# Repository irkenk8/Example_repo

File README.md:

# Example_repo
Here are all the project folders

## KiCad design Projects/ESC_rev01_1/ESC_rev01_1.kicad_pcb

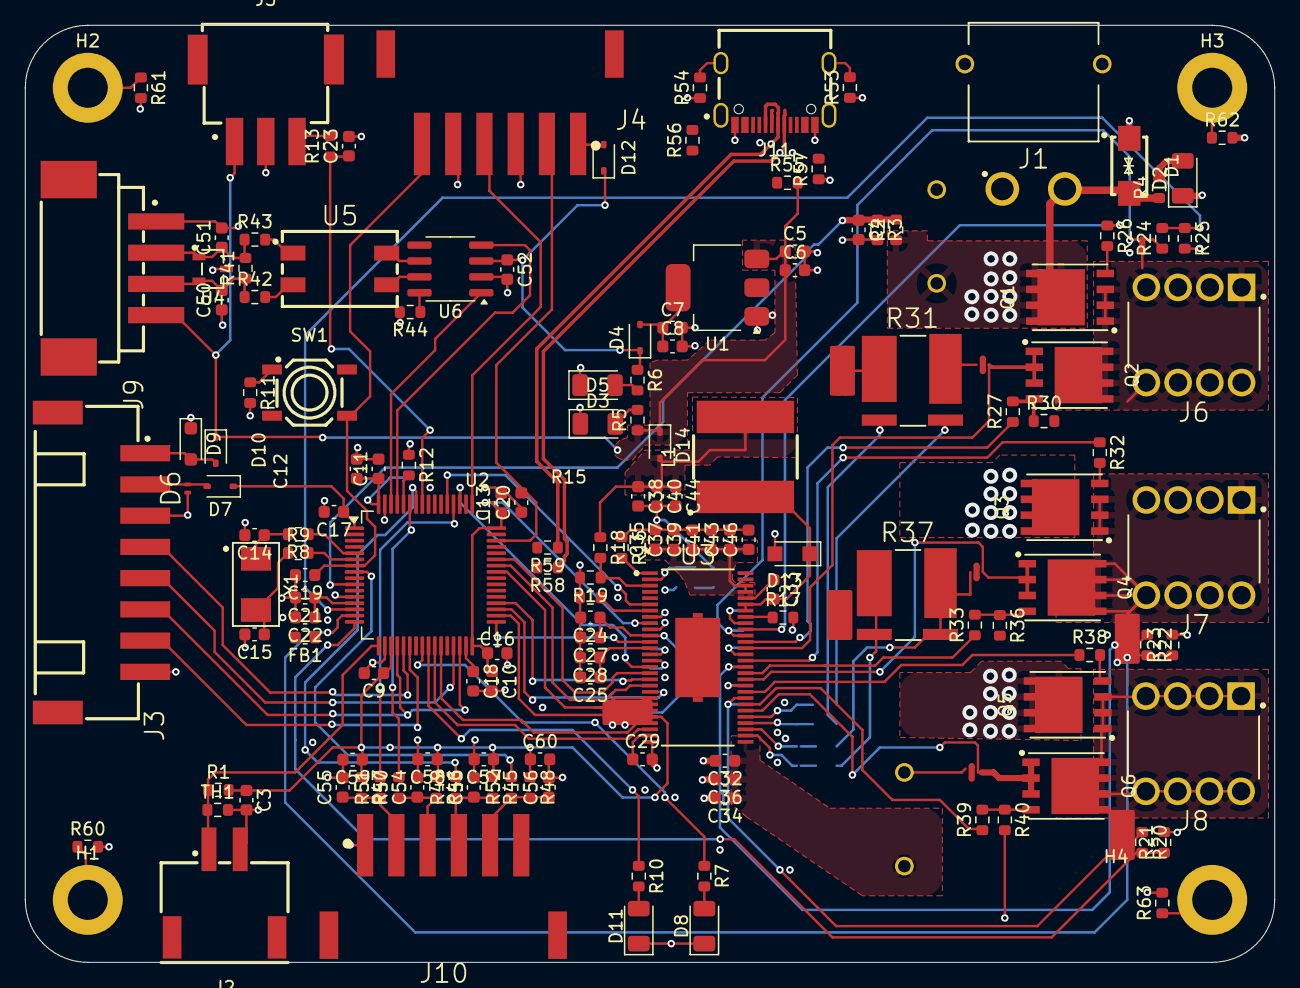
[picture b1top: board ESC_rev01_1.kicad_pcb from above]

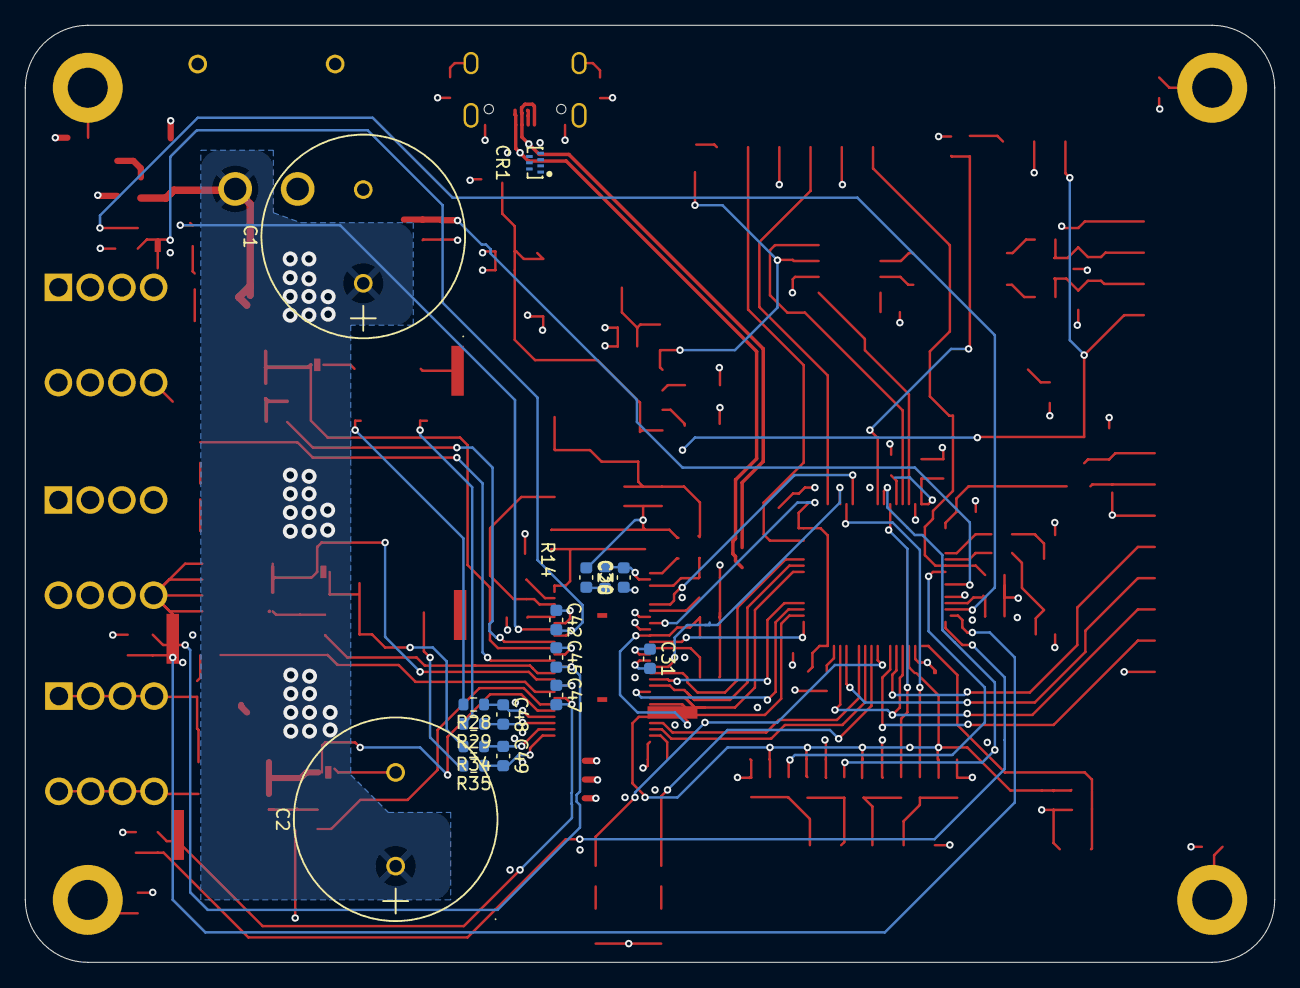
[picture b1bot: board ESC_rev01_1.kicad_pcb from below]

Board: 4 copper layers, 100.0 x 75.0 mm, 179 parts (16 on the bottom side), 125 nets.

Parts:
C1, C2: LKMI2501K821MF; CAPPRD750W80D1600H2500
C3, C4, C10, C11, C12, C13, C16, C17, C19, C21, C23, C33, C42, C45, C47, C57, C58, C59, C60: 100n; C_0603_1608Metric
C5, C6, C7, C8, C22: 1u; C_0603_1608Metric
C9, C32, C34, C35, C36, C37, C38, C39, C40, C41, C43, C44, C46: 10u; C_0603_1608Metric
C14, C15: 10p; C_0603_1608Metric
C18, C20, C24, C25, C27, C28, C29, C48, C52: 2u2; C_0603_1608Metric
C26: 6n8; C_0603_1608Metric
C30: 120p; C_0603_1608Metric
C31: 22n; C_0603_1608Metric
C49: 2n2; C_0603_1608Metric
C50, C51: 60p; C_0603_1608Metric
C53, C54, C55, C56: 4n7; C_0603_1608Metric
CR1: PUSB3AB6Z; XSON-7_L2.2-W1.2-P0.50-BL
D1: SMA6J60CA-Q; SMA_L4.4-W2.8-LS5.1-BI
D2, D3, D5, D8: LED_G; LED_1206_3216Metric
D4, D7, D10, D12, D14: BAT60A; D_SOD-323
D6: PESD3V3X1BL; D_SOD-882_BI
D9: SD05C-7; D_SOD-323_HandSoldering
D11: LED_R; LED_1206_3216Metric
D13: PMEG6020ER; Nexperia_CFP3_SOD-123W
FB1: FerriteBead; L_0603_1608Metric
H1, H2, H3, H4: MountingHole_Pad; MountingHole_3.2mm_M3_DIN965_Pad
J1: XT30PW-M; CONN-TH_XT30PW-M
J2: XH-2PWBPZ; CONN-SMD_XH-2PWBPZ
J3: XH-2PWBPZ; CONN-SMD_8P-P2.50_HX25003-8AWB
J4, J10: Conn_01x06_2mnt; CONN_DEALON_XH-6PWB
J5: Conn_01x03; CONN-SMD_XH-3AWB
J6, J7, J8: Conn_01x01; WE_7461084
J9: Conn_01x04_2mnt; CONN-SMD_S4B-XH-SM4-TB-LF-SN
J11: TYPE-C-31-M-12; USB-C_SMD-TYPE-C-31-M-12_1
L1: 22u; IND-SMD_L7.8-W7.8_SDR0805
NT1, NT2, NT5, NT8: NetTie_2; NetTie-2_SMD_Pad0.5mm
NT3, NT4, NT6, NT7, NT9: NetTie_2; NetTie-2_SMD_Pad_4.0x2.0mm
Q1, Q2, Q3, Q4, Q5, Q6: HSBA15810C; PQFN-8_L6.0-W5.0-P1.27-LS6.0-BL
R1, R3, R11, R13, R45, R46, R47: 2k2; R_0603_1608Metric
R2, R4, R30, R36, R40: 39k; R_0603_1608Metric
R5, R6, R9, R10: 1k; R_0603_1608Metric
R7, R8, R52, R53, R54, R55, R60, R61, R62, R63: 0R; R_0603_1608Metric
R12: 100k; R_0603_1608Metric
R14: 16k2; R_0603_1608Metric
R15, R44, R48, R49, R50, R51: 10k; R_0603_1608Metric
R16: 205k; R_0603_1608Metric
R17: 1M; R_0603_1608Metric
R18, R20, R22, R24: 18k; R_0603_1608Metric
R19, R21, R23, R25: 3k3; R_0603_1608Metric
R26, R27, R32, R33, R38, R39: 4R7; R_0603_1608Metric
R28, R29, R34, R35: 100R; R_0603_1608Metric
R31, R37: 0R001; RES_VISHAY_WSLP27261L000
R41: 120R; R_0603_1608Metric
R42, R43: 10R; R_0603_1608Metric
R56, R57: 5k1; R_0603_1608Metric
R58, R59: 22R; R_0603_1608Metric
SW1: PTS526SK15SMTR2LFS; SW-SMD_4P-L5.2-W5.2-P3.70-LS6.4
TH1: 10k; R_0603_1608Metric
U1: AMS1117-3.3; SOT-223-3_TabPin2
U2: STM32F405RGTx; LQFP-64_10x10mm_P0.5mm
U3: DRV8302DCA; DCA56_6P35X3P61
U4: ESDCAN24-2BLY; SOT-23-3_L3.0-W1.7-P0.95-LS2.9-BR
U5: 744227S; FILTER-SMD_4P-L9.2-W6.0-P2.54-TL
U6: SN65HVD230; SOIC-8_3.9x4.9mm_P1.27mm
Y1: 8M 10ppm X50328MSB2GI; CRYSTAL-SMD_L5.0-W3.2

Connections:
+3V3: C3.1, C9.1, C10.1, C11.1, C12.1, C13.1, C16.1, C17.1, C52.1, C57.1, C58.1, C59.1, C60.1, D4.1 (K), D7.1 (K), D12.1 (K), FB1.2, R6.1, R45.1, R46.1, R47.1, R48.1, TH1.1, U2.1 (VBAT), U2.19 (VDD), U2.32 (VDD), U2.48 (VDD), U2.64 (VDD), U3.9 (M_OC), U3.24 (REF), U6.3 (VCC)
+5V: C5.1, C6.1, D10.1 (K), D14.1 (K), J5.1, J9.4, J10.1, R5.1, R55.2, U1.3 (VI)
+VDC: C1.1, C2.1, C32.1, C34.1, C35.1, C36.1, C37.1, C39.1, C41.1, C43.1, C46.1, D1.2 (A), J1.2 (+), Q1.5 (D), Q3.5 (D), Q5.5 (D), R2.1, R4.1, U3.29 (PVDD1), U3.53 (PVDD2), U3.54 (PVDD2)
/[03] - STEP-DOWN/+3V3_IC: C7.1, C8.1, D4.2 (A), U1.2 (VO)
/[04] - MCU/+3V3_A: C21.1, C22.1, FB1.1, U2.13 (VDDA)
/[04] - MCU/+3V3_COM: D6.2 (A2), D7.2 (A), J3.2
/[04] - MCU/+3V3_DBG: D12.2 (A), J4.1
/[04] - MCU/+5V_COM: D9.2 (A2), D10.2 (A), J3.1
/[04] - MCU/BOOT: R12.2, U2.60 (BOOT0)
/[04] - MCU/LED_GREEN: R9.1, U2.24 (PC4)
/[04] - MCU/LED_RED: R10.1, U2.25 (PC5)
/[04] - MCU/MISO_ADC_EXT2: J3.7, U2.22 (PA6)
/[04] - MCU/NRST: C19.1, J4.6, SW1.3, SW1.4, U2.7 (NRST)
/[04] - MCU/PH_0: C14.1, R7.2, Y1.1
/[04] - MCU/PH_0_P: R7.1, U2.5 (PH0)
/[04] - MCU/PH_1: C15.1, R8.1, Y1.2
/[04] - MCU/PH_1_P: R8.2, U2.6 (PH1)
/[04] - MCU/RX_SCL_MOSI: J3.5, U2.29 (PB10), U2.38 (PC7)
/[04] - MCU/SCK_ADC_EXT: J3.4, U2.21 (PA5)
/[04] - MCU/SERVO: C23.1, R13.1, U2.57 (PB5)
/[04] - MCU/SWCLK: J4.4, U2.49 (PA14)
/[04] - MCU/SWDIO: J4.2, U2.46 (PA13)
/[04] - MCU/TX_SDA_NSS: J3.6, U2.20 (PA4), U2.30 (PB11), U2.37 (PC6)
/[04] - MCU/VCAP_1: C18.1, U2.31 (VCAP_1)
/[04] - MCU/VCAP_2: C20.1, U2.47 (VCAP_2)
/[05] - MOSFET DRIVER/+5V_DRV: C38.1, C40.1, C44.1, D14.2 (A), L1.2, R18.1
/[05] - MOSFET DRIVER/BIAS: R17.1, U3.49 (BIAS)
/[05] - MOSFET DRIVER/BST_A: C42.1, U3.48 (BST_A)
/[05] - MOSFET DRIVER/BST_B: C45.1, U3.43 (BST_B)
/[05] - MOSFET DRIVER/BST_BK: C33.1, U3.52 (BST_BK)
/[05] - MOSFET DRIVER/BST_C: C47.1, U3.38 (BST_C)
/[05] - MOSFET DRIVER/COMP: C30.2, R14.2, U3.2 (COMP)
/[05] - MOSFET DRIVER/CP1: C31.1, U3.14 (CP1)
/[05] - MOSFET DRIVER/CP2: C31.2, U3.15 (CP2)
/[05] - MOSFET DRIVER/DTC: R15.2, U3.7 (DTC)
/[05] - MOSFET DRIVER/DVDD: NT1.1, U3.23 (DVDD)
/[05] - MOSFET DRIVER/OC_ADJ: C24.1, C27.1, NT1.2, U3.11 (OC_ADJ)
/[05] - MOSFET DRIVER/PH: C33.2, D13.1 (K), L1.1, U3.50 (PH), U3.51 (PH)
/[05] - MOSFET DRIVER/RT_CLK: R16.2, U3.1 (RT_CLK)
/[05] - MOSFET DRIVER/VSENSE: R18.2, R19.1, U3.3 (VSENSE)
/[06] - MOSFETs/M_H1_RG: Q1.4 (G), R26.2
/[06] - MOSFETs/M_H2_RG: Q3.4 (G), R32.2
/[06] - MOSFETs/M_H3_RG: Q5.4 (G), R38.2
/[06] - MOSFETs/M_L1_RG: Q2.4 (G), R27.2, R30.1
/[06] - MOSFETs/M_L2_RG: Q4.4 (G), R33.2, R36.1
/[06] - MOSFETs/M_L3_RG: Q6.4 (G), R39.2, R40.1
/[06] - MOSFETs/PHASE_1: J6.1, NT2.2, Q1.1 (S), Q1.2 (S), Q1.3 (S), Q2.5 (D)
/[06] - MOSFETs/PHASE_2: J7.1, NT5.2, Q3.1 (S), Q3.2 (S), Q3.3 (S), Q4.5 (D)
/[06] - MOSFETs/PHASE_3: J8.1, NT8.2, Q5.1 (S), Q5.2 (S), Q5.3 (S), Q6.5 (D)
/[06] - MOSFETs/SH1_N: NT3.1, R28.2, R31.2
/[06] - MOSFETs/SH1_P: NT4.2, R29.2, R31.1
/[06] - MOSFETs/SH2_N: NT6.1, R34.2, R37.2
/[06] - MOSFETs/SH2_P: NT7.2, R35.2, R37.1
/[07] - CAN/CAN_N: U5.4, U6.6 (CANL)
/[07] - CAN/CAN_P: U5.3, U6.7 (CANH)
/[07] - CAN/C_CAN_N: C51.1, J9.2, R41.2, R43.1, U4.1
/[07] - CAN/C_CAN_P: C50.2, J9.3, R41.1, R42.1, U4.2
/[07] - CAN/R_CAN_N: R43.2, U5.1
/[07] - CAN/R_CAN_P: R42.2, U5.2
/[08] - FILTERS/HALL_1_IN: C53.1, J10.3, R45.2, R49.1
/[08] - FILTERS/HALL_2_IN: C54.1, J10.4, R46.2, R50.1
/[08] - FILTERS/HALL_3_IN: C55.1, J10.5, R47.2, R51.1
/[08] - FILTERS/TEMP_IN: C56.1, J10.2, R48.2, R52.1
/[09] - USB/+5V-C: CR1.3 (IO2), CR1.5 (IO4), J11.A4B9 (VBUS), J11.B4A9 (VBUS), R55.1
/[09] - USB/CC1: CR1.4 (IO3), J11.A5 (CC1), R57.2
/[09] - USB/CC2: CR1.1 (IO1), J11.B5 (CC2), R56.2
/[09] - USB/USB-C_N: CR1.7 (IO6), J11.A7 (DN1), J11.B7 (DN2), R58.1
/[09] - USB/USB-C_P: CR1.6 (IO5), J11.A6 (DP1), J11.B6 (DP2), R59.1
ADC_TEMP: J2.1, R1.2, TH1.2, U2.17 (PA3)
AN_IN: C4.1, R2.2, R3.1, U2.10 (PC2)
BR_SO1: U2.27 (PB1), U3.25 (SO1)
BR_SO2: U2.26 (PB0), U3.26 (SO2)
CAN_RX: U2.61 (PB8), U6.4 (R)
CAN_TX: U2.62 (PB9), U6.1 (D)
DC_CAL: U2.33 (PB12), U3.12 (DC_CAL)
EN_GATE: U2.51 (PC10), U3.16 (EN_GATE)
FAULT: U2.53 (PC12), U3.6 (*FAULT)
GND: C1.2, C2.2, C3.2, C4.2, C5.2, C6.2, C7.2, C8.2, C9.2, C10.2, C11.2, C12.2, C13.2, C14.2, C15.2, C16.2, C17.2, C18.2, C19.2, C20.2, C21.2, C22.2, C23.2, C24.2, C25.2, C26.1, C27.2, C28.2, C29.2, C30.1, C32.2, C34.2, C35.2, C36.2, C37.2, C38.2, C39.2, C40.2, C41.2, C43.2, C44.2, C46.2, C50.1, C51.2, C52.2, C53.2, C54.2, C55.2, C56.2, C57.2, C58.2, C59.2, C60.2, CR1.2 (GND), D1.1 (K), D2.1 (K), D3.1 (K), D5.1 (K), D6.1 (A1), D8.1 (K), D9.1 (A1), D11.1 (K), D13.2 (A), J1.1 (-), J2.2, J3.3, J3.8, J4.3, J4.5, J5.2, J9.1, J10.6, J11.A1B12 (GND), J11.B1A12 (GND), NT4.1, NT7.1, NT9.1, R1.1, R3.2, R11.2, R12.1, R15.1, R16.1, R17.2, R19.2, R21.2, R23.2, R25.2, R30.2, R36.2, R40.2, R44.2, R53.1, R54.1, R56.1, R57.1, R60.2, R61.2, R62.2, R63.2, U1.1 (GND), U2.12 (VSSA), U2.18 (VSS), U2.63 (VSS), U3.8 (M_PWM), U3.10 (GAIN), U3.28 (AGND), U3.57 (EPAD), U4.3, U6.2 (GND)
H1: U2.43 (PA10), U3.17 (INH_A)
H1_LOW: NT3.2, Q2.1 (S), Q2.2 (S), Q2.3 (S), U3.44 (SL_A)
H1_VS: C42.2, NT2.1, R24.1, U3.46 (SH_A)
H2: U2.42 (PA9), U3.19 (INH_B)
H2_LOW: NT6.2, Q4.1 (S), Q4.2 (S), Q4.3 (S), U3.39 (SL_B)
H2_VS: C45.2, NT5.1, R22.1, U3.41 (SH_B)
H3: U2.41 (PA8), U3.21 (INH_C)
H3_LOW: NT9.2, Q6.1 (S), Q6.2 (S), Q6.3 (S), U3.34 (SL_C)
H3_VS: C47.2, NT8.1, R20.1, U3.36 (SH_C)
HALL_1_OUT: R49.2, U2.58 (PB6)
HALL_2_OUT: R50.2, U2.59 (PB7)
HALL_3_OUT: R51.2, U2.52 (PC11)
L1: U2.36 (PB15), U3.18 (INL_A)
L2: U2.35 (PB14), U3.20 (INL_B)
L3: U2.34 (PB13), U3.22 (INL_C)
M_H1: R26.1, U3.47 (GH_A)
M_H2: R32.1, U3.42 (GH_B)
M_H3: R38.1, U3.37 (GH_C)
M_L1: R27.1, U3.45 (GL_A)
M_L2: R33.1, U3.40 (GL_B)
M_L3: R39.1, U3.35 (GL_C)
unnamed: C26.2, R14.1
unnamed: D2.2 (A), R4.2
unnamed: D3.2 (A), R5.2
unnamed: D5.2 (A), R6.2
unnamed: D8.2 (A), R9.2
unnamed: D11.2 (A), R10.2
unnamed: H1.1, R60.1
unnamed: H2.1, R61.1
unnamed: H3.1, R62.1
unnamed: H4.1, R63.1
unnamed: J5.3, R13.2
unnamed: J11.1 (EH), J11.2 (EH), J11.3 (EH), J11.4 (EH), R53.2, R54.2
unnamed: R11.1, SW1.1, SW1.2
unnamed: C29.1, U3.27 (AVDD)
unnamed: C25.1, C28.1, U3.13 (GVDD)
unnamed: R44.1, U6.8 (Rs)
S1_N: C48.1, R28.1, U3.33 (SN1)
S1_P: C48.2, R29.1, U3.32 (SP1)
S2_N: C49.1, R34.1, U3.31 (SN2)
S2_P: C49.2, R35.1, U3.30 (SP2)
SENS1: R20.2, R21.1, U2.16 (PA2)
SENS2: R22.2, R23.1, U2.15 (PA1)
SENS3: R24.2, R25.1, U2.14 (PA0)
TEMP_MOTOR: R52.2, U2.8 (PC0)
USB_DN: R58.2, U2.44 (PA11)
USB_DP: R59.2, U2.45 (PA12)

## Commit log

2025-09-16 Update 01
    Changes in the repository structure
2025-09-16 Update 02
    Added Dario Fresu kiCad templates
2025-09-17 Update 03
    Example project created
2025-09-17 Update 04
    Adding block diagram
2025-09-18 Update 05
    MCU schematic created
2025-09-18 Update 06
    MOSFET DRIVER schematic created
2025-09-22 Update 07
    Schematic is ready
    INPUT PROTECTION schematic created
    MOSFETs schematic created
    CAN schematic created
    FILTERs schematic created
    MECHANICAL schematic created
2025-09-23 Update 08
    Component placement is almost done
    Check one more time and correct if needed
2025-10-10 Update 09
    Components placement finished
2025-10-11 Update 10
    -Rules added (for signal, differential pair USB and CAN, power traces)
    -Stackup corrected
2025-10-11 Update 11
    Draft routing - diff signals and power
2025-10-15 Update 12
    Continue routing
2026-02-06 Update 01
